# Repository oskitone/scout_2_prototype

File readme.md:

# scout_2_prototype

This is a prototype around a PCB I sent off to fab in March 2022... that I'm slowly bringing back to life. I'm kind of using it as a springboard for the next thing, whatever that is and whenever it happens!

Very much work-in-progress. License will be MIT like other kits.

Forked from scout's [2-25_keys](https://github.com/oskitone/scout/tree/2-25_keys) branch

## In this repo

- Kicad project
- OpenSCAD for scaffolding and keys models
- STLs for 3D-printing

## Goals

### Overarching Oskitone design goals

- Easy to solder. Only through-hole parts, even if it limits functionality.
- Easy to change. Code can be edited with free software and cheap hardware.
- Easy to play. No hidden menus, secret key combos, or overloading. One control per one function.
- Easy to understand. Code should be relatively accessible to anybody familiar with Arduino.
- Easy to hack. Programming header (TODO? hmm), usual open source ethos stuff.

### And specific to the next ~synth

- Polyphony
  - Per my ability, four is a reasonable number of notes to play simultaneously. Three is okay but would be frustrating. Two would be funny?
  - Anyway, four notes is what D9-12 are attempting. At the time, I was thinking I could tack some math around millis() and make the square waves manually... maybe use an interrupt timer? My pin choice seems random, and there're probably better choices.
- Any kind of musical connectivity
  - MIDI
    - USB is modern but circular DIN connectors are standard and inarguably answer the question "But can it do MIDI?!"
    - I think I'd also need non-DIP chips to do USB MIDI so that's out
    - I don't know if both IN and OUT are necessary or which to prefer if there can only be one. DIN connectors are big; [TRS MIDI](https://minimidi.world/) is an option.
  - Control Voltage
    - I'm open to this but don't really know the scene well enough to know what would be good. If it's easy to add, sure.
- Support for Mozzi w/o shipping w/ it
  - I want it to still feel solidly like an Oskitone instrument, for better and no doubt worse. Blame ["not invented here" syndrome](https://en.wikipedia.org/wiki/Not_invented_here).
  - Mozzi is cool as hell but it does require reading docs, which maybe breaks the "easy to understand" goal.
  - <del>Plus, even if I wanted to, I don't think Mozzi's license would permit me selling kits w/ it.</del> [Looks like they're GNU LGPL now](https://github.com/sensorium/Mozzi/pull/240), so may be okay.
  - That having been said, I want to engender "side-loading" things like this and make swapping to Mozzi straightforward, especially if the barrier to entry is low. So minimally it needs the right pins, an output filter, maybe other changes too.
- More musically useful than the Scout
  - Same size keys but as many as I can fit on a Prusa.
  - A semblance of control with analog input pots. Currently doing octave and glide.
  - Glide is fun but will be weird if/when polyphony is introduced. Could do poly only at 0 glide

## TODO / known issues / things for next rev

- 3D prints
  - Octave control really needs detents or some kinda tactile feedback on rotation.
- For next rev
  - More key mounting screw holes? Key bed subassembly with multiple parts
  - Rethink headphone output in signal path to minimize amplified noise
  - 386 bass boost?
  - Fix PROOF silkscreen text on back
  - Try shift register for 8 outputs? To resistor array!
  - Ditch MIDI in. Keep MIDI out but use TRS for smaller footprint
  - See if speaker can fit in new space?
- Tiny speaker is quick to distort and has no low end
- Make it clear/explicit how FUNCTION_INDICATOR_LED is used as "hanging" indicator. Right now, it's incidental.

Anything else?

https://github.com/user-attachments/assets/99f4f9d2-c58f-4821-b225-9032d2b2e849

## Uploading new code

The UART header [works the same as the OG Scout](https://oskitone.github.io/scout/change-the-arduino-code).

The cable's black wire should be on the left and green on the right.

## BOM

| Designator           | Footprint                                         | Quantity | Designation        |
| -------------------- | ------------------------------------------------- | -------- | ------------------ |
| SW1-SW25             | SW_PUSH_6mm                                       | 25       | SPST               |
| BT1                  | PinHeader_1x02_P2.54mm_Vertical                   | 1        | 4.5v               |
| LS1                  | PinHeader_1x02_P2.54mm_Vertical                   | 1        | Speaker            |
| RV1                  | Potentiometer_Bourns_PTV09A-1_Single_Vertical     | 1        | 10k Log            |
| Y1                   | Resonator-3Pin_W7.0mm_H2.5mm                      | 1        | 16.00MHz           |
| U2                   | DIP-8_W7.62mm                                     | 1        | LM386              |
| R4,R5,R7,R6          | R_Axial_DIN0207_L6.3mm_D2.5mm_P10.16mm_Horizontal | 4        | 10K                |
| J1                   | AUDIO-JACK                                        | 1        | AudioJack2_SwitchT |
| C2,C4,C5             | C_Disc_D5.0mm_W2.5mm_P5.00mm                      | 3        | .1uF               |
| C6,C1                | CP_Radial_D8.0mm_P3.50mm                          | 2        | 220uF              |
| U1                   | DIP-28_W7.62mm                                    | 1        | ATmega328P-PU      |
| D1-D25,D27           | D_DO-41_SOD81_P10.16mm_Horizontal                 | 26       | D                  |
| J2                   | PinHeader_1x06_P2.54mm_Horizontal                 | 1        | Conn_01x06_Male    |
| R8                   | R_Axial_DIN0207_L6.3mm_D2.5mm_P10.16mm_Horizontal | 1        | 1m                 |
| R9,R13               | R_Axial_DIN0207_L6.3mm_D2.5mm_P10.16mm_Horizontal | 2        | 10k                |
| R10,R1,R11,R3,R2,R12 | R_Axial_DIN0207_L6.3mm_D2.5mm_P10.16mm_Horizontal | 6        | 220                |
| D26                  | LED_D5.0mm-4_RGB_Staggered_Pins                   | 1        | LED_CRGB           |
| J4,J3                | DIN5-RA-PTH                                       | 2        | DIN5               |
| SW26                 | SW_Slide_1P2T_CK_OS102011MS2Q                     | 1        | SW_SPST            |
| RV2,RV3              | Potentiometer_Bourns_PTV09A-1_Single_Vertical     | 2        | 10k                |
| C3                   | CP_Radial_D5.0mm_P2.00mm                          | 1        | 1uF                |
| U3                   | DIP-8_W7.62mm                                     | 1        | 6N138              |

## Schematics

TODO: update to PROOF B

## 3D Models

Normally I'd put them on thingiverse/etc, but here they're included in the repo in the `stls` folder.

### OpenSCAD dependencies

Assumes `parts_cafe` is in a sibling directory and is up to date on the `main` branch. Here's how I've got it:

    \ oskitone
        \ parts_cafe
        \ scout_2_prototype

You'll also need to install the [Orbitron](https://fonts.google.com/specimen/Orbitron) font.

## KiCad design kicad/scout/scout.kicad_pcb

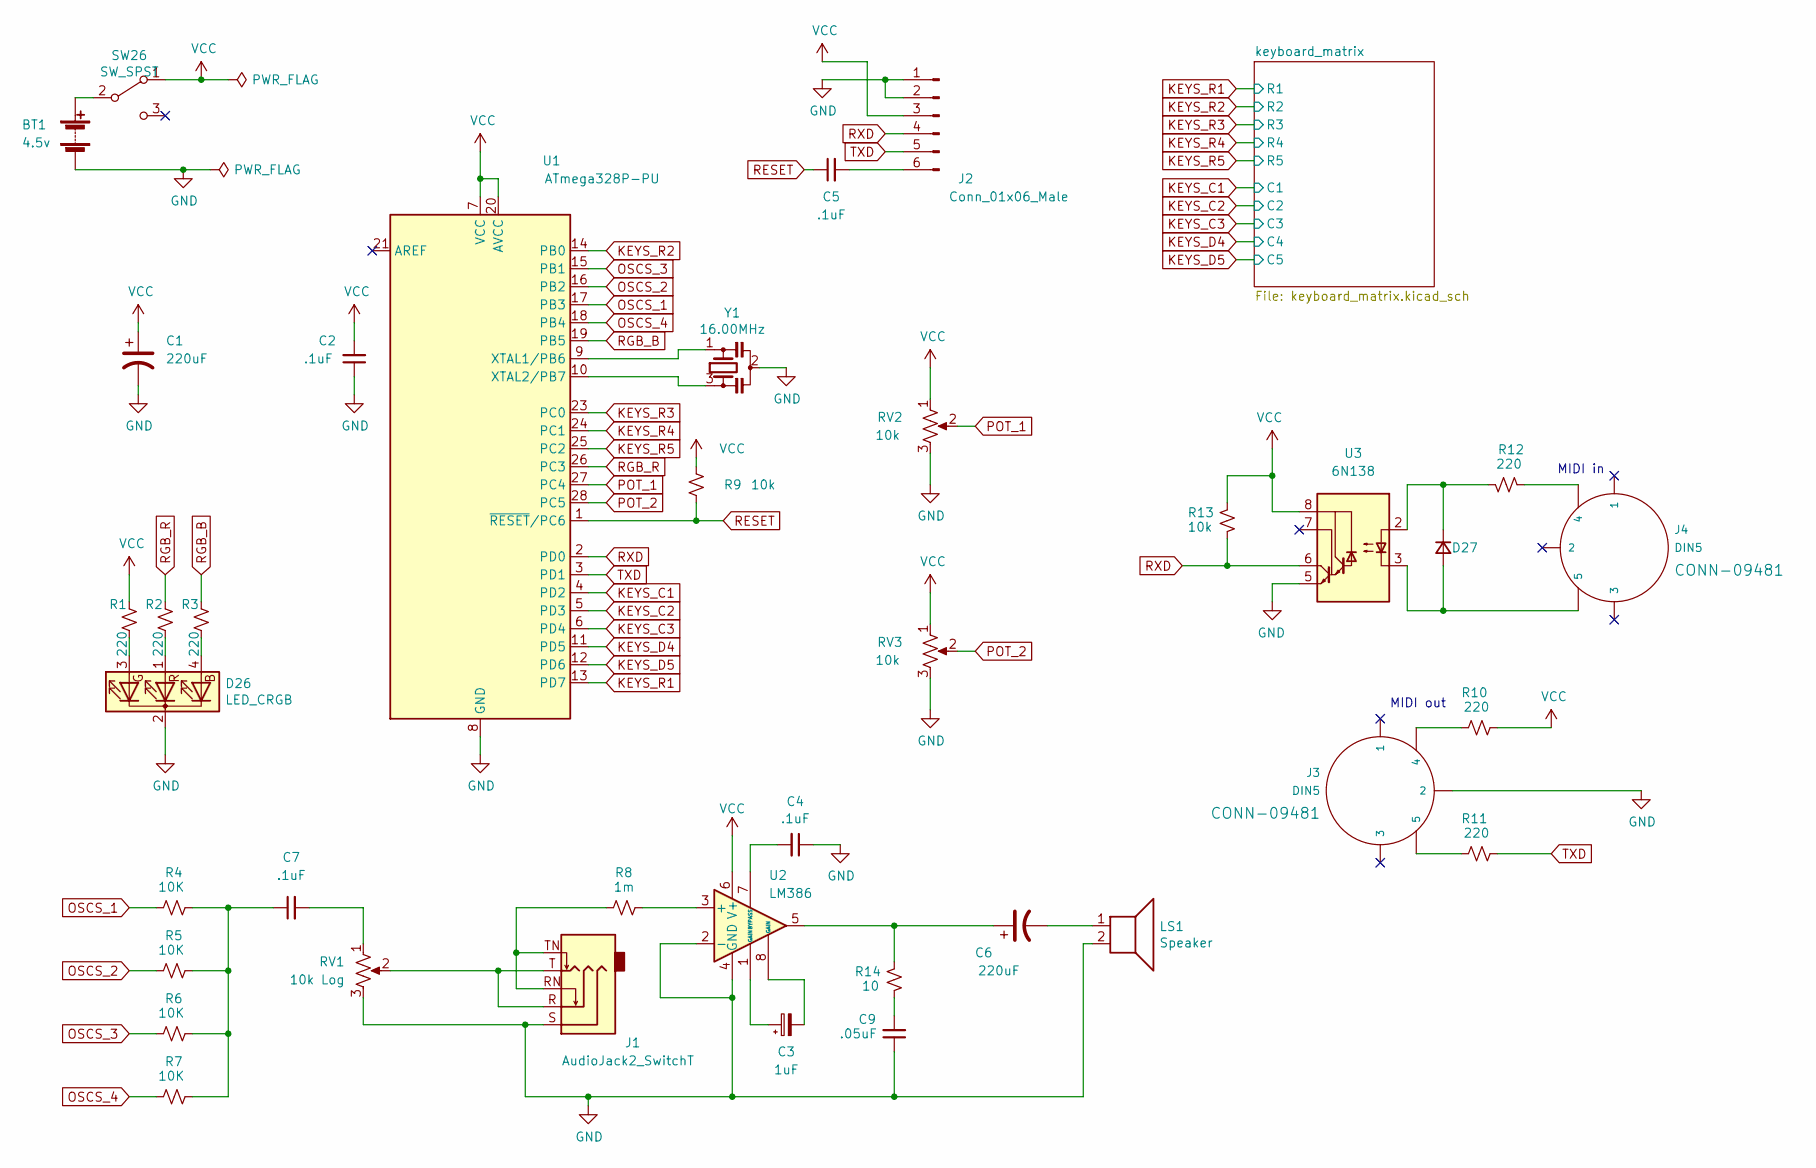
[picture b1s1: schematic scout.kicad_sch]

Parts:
BT1: 4.5v; PinHeader_1x02_P2.54mm_Vertical
C1, C6: 220uF; CP_Radial_D8.0mm_P3.50mm
C2, C4, C5, C7: .1uF; C_Disc_D5.0mm_W2.5mm_P5.00mm
C3: 1uF; CP_Radial_D5.0mm_P2.00mm
C9: .05uF; C_Disc_D5.0mm_W2.5mm_P5.00mm
D26: LED_CRGB; LED_D5.0mm-4_RGB_Staggered_Pins
D27: D; D_DO-41_SOD81_P10.16mm_Horizontal
J1: AudioJack2_SwitchT; AUDIO-JACK
J2: Conn_01x06_Male; PinHeader_1x06_P2.54mm_Horizontal
J3, J4: DIN5; DIN5-RA-PTH
LS1: Speaker; PinHeader_1x02_P2.54mm_Vertical
R1, R2, R3, R10, R11, R12: 220; R_Axial_DIN0207_L6.3mm_D2.5mm_P10.16mm_Horizontal
R4, R5, R6, R7: 10K; R_Axial_DIN0207_L6.3mm_D2.5mm_P10.16mm_Horizontal
R8: 1m; R_Axial_DIN0207_L6.3mm_D2.5mm_P10.16mm_Horizontal
R9, R13: 10k; R_Axial_DIN0207_L6.3mm_D2.5mm_P10.16mm_Horizontal
R14: 10; R_Axial_DIN0207_L6.3mm_D2.5mm_P10.16mm_Horizontal
RV1: 10k Log; Potentiometer_Bourns_PTV09A-1_Single_Vertical
RV2, RV3: 10k; Potentiometer_Bourns_PTV09A-1_Single_Vertical
SW26: SW_SPST; SW_Slide_1P2T_CK_OS102011MS2Q
U1: ATmega328P-PU; DIP-28_W7.62mm
U2: LM386; DIP-8_W7.62mm
U3: 6N138; DIP-8_W7.62mm
Y1: 16.00MHz; Resonator-3Pin_W7.0mm_H2.5mm

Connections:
GND: BT1.2 (-), C1.2, C2.1, C4.1, C9.1, D26.2 (K), J1.S, J2.1, J2.2, J3.2, LS1.2, RV1.3, RV2.3, RV3.3, U1.8 (GND), U1.22 (GND), U2.2 (-), U2.4 (GND), U3.5 (GND), Y1.2
KEYS_C1: U1.4 (PD2); also elsewhere on the board
KEYS_C2: U1.5 (PD3); also elsewhere on the board
KEYS_C3: U1.6 (PD4); also elsewhere on the board
KEYS_D4: U1.11 (PD5); also elsewhere on the board
KEYS_D5: U1.12 (PD6); also elsewhere on the board
KEYS_R1: U1.13 (PD7); also elsewhere on the board
KEYS_R2: U1.14 (PB0); also elsewhere on the board
KEYS_R3: U1.23 (PC0); also elsewhere on the board
KEYS_R4: U1.24 (PC1); also elsewhere on the board
KEYS_R5: U1.25 (PC2); also elsewhere on the board
unnamed: BT1.1 (+), SW26.2 (B)
unnamed: C3.1, U2.1 (GAIN)
unnamed: C3.2, U2.8 (GAIN)
unnamed: C6.1, R14.1, U2.5
unnamed: C6.2, LS1.1
unnamed: C7.1, R4.2, R5.2, R6.2, R7.2
unnamed: C7.2, RV1.1
unnamed: C9.2, R14.2
unnamed: D26.4 (BA), R3.2
unnamed: D26.1 (GA), R2.2
unnamed: D26.3 (RA), R1.2
unnamed: D27.2 (A), J4.5, U3.3 (C2)
unnamed: D27.1 (K), R12.2, U3.2 (C1)
unnamed: J1.R, J1.T, RV1.2
unnamed: J1.RN, J1.TN, R8.1
unnamed: C5.2, J2.6
unnamed: J3.4, R10.1
unnamed: J3.5, R11.1
unnamed: J4.4, R12.1
unnamed: U1.9 (XTAL1/PB6), Y1.1
unnamed: U1.10 (XTAL2/PB7), Y1.3
unnamed: R8.2, U2.3 (+)
unnamed: C4.2, U2.7 (BYPASS)
OSCS_1: R4.1, U1.17 (PB3)
OSCS_2: R5.1, U1.16 (PB2)
OSCS_3: R6.1, U1.15 (PB1)
OSCS_4: R7.1, U1.18 (PB4)
POT_1: RV2.2, U1.27 (PC4)
POT_2: RV3.2, U1.28 (PC5)
RESET: C5.1, R9.2, U1.1 (~RESET/PC6)
RGB_B: R3.1, U1.19 (PB5)
RGB_R: R2.1, U1.26 (PC3)
RXD: J2.4, R13.2, U1.2 (PD0), U3.6 (VO2)
TXD: J2.5, R11.2, U1.3 (PD1)
VCC: C1.1, C2.2, J2.3, R1.1, R9.1, R10.2, R13.1, RV2.1, RV3.1, SW26.1 (A), U1.7 (VCC), U1.20 (AVCC), U2.6 (V+), U3.8 (VCC)

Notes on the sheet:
MIDI in
MIDI out

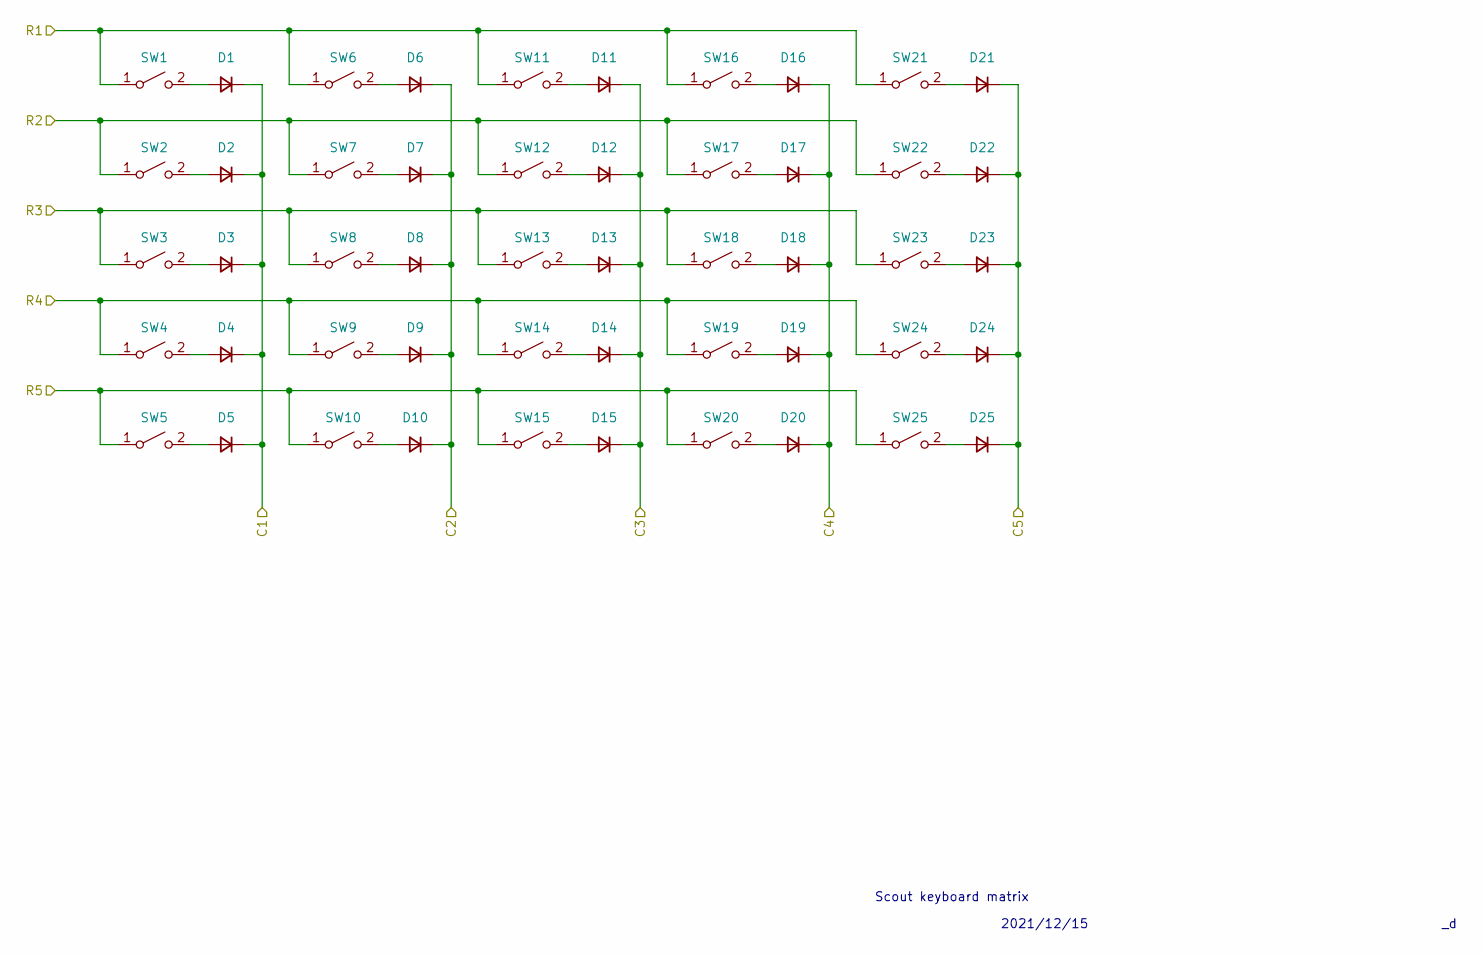
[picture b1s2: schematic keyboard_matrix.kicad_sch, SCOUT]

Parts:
D1, D2, D3, D4, D5, D6, D7, D8, D9, D10, D11, D12, D13, D14, D15, D16, D17, D18, D19, D20, D21, D22, D23, D24, D25: 1N4148; D_DO-41_SOD81_P10.16mm_Horizontal
SW1, SW2, SW3, SW4, SW5, SW6, SW7, SW8, SW9, SW10, SW11, SW12, SW13, SW14, SW15, SW16, SW17, SW18, SW19, SW20, SW21, SW22, SW23, SW24, SW25: SPST; SW_PUSH_6mm

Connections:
KEYS_C1: D1.1 (K), D2.1 (K), D3.1 (K), D4.1 (K), D5.1 (K); also elsewhere on the board
KEYS_C2: D6.1 (K), D7.1 (K), D8.1 (K), D9.1 (K), D10.1 (K); also elsewhere on the board
KEYS_C3: D11.1 (K), D12.1 (K), D13.1 (K), D14.1 (K), D15.1 (K); also elsewhere on the board
KEYS_D4: D16.1 (K), D17.1 (K), D18.1 (K), D19.1 (K), D20.1 (K); also elsewhere on the board
KEYS_D5: D21.1 (K), D22.1 (K), D23.1 (K), D24.1 (K), D25.1 (K); also elsewhere on the board
KEYS_R1: SW1.1 (A), SW6.1 (A), SW11.1 (A), SW16.1 (A), SW21.1 (A); also elsewhere on the board
KEYS_R2: SW2.1 (A), SW7.1 (A), SW12.1 (A), SW17.1 (A), SW22.1 (A); also elsewhere on the board
KEYS_R3: SW3.1 (A), SW8.1 (A), SW13.1 (A), SW18.1 (A), SW23.1 (A); also elsewhere on the board
KEYS_R4: SW4.1 (A), SW9.1 (A), SW14.1 (A), SW19.1 (A), SW24.1 (A); also elsewhere on the board
KEYS_R5: SW5.1 (A), SW10.1 (A), SW15.1 (A), SW20.1 (A), SW25.1 (A); also elsewhere on the board
unnamed: D1.2 (A), SW1.2 (B)
unnamed: D2.2 (A), SW2.2 (B)
unnamed: D3.2 (A), SW3.2 (B)
unnamed: D4.2 (A), SW4.2 (B)
unnamed: D5.2 (A), SW5.2 (B)
unnamed: D6.2 (A), SW6.2 (B)
unnamed: D7.2 (A), SW7.2 (B)
unnamed: D8.2 (A), SW8.2 (B)
unnamed: D9.2 (A), SW9.2 (B)
unnamed: D10.2 (A), SW10.2 (B)
unnamed: D11.2 (A), SW11.2 (B)
unnamed: D12.2 (A), SW12.2 (B)
unnamed: D13.2 (A), SW13.2 (B)
unnamed: D14.2 (A), SW14.2 (B)
unnamed: D15.2 (A), SW15.2 (B)
unnamed: D16.2 (A), SW16.2 (B)
unnamed: D17.2 (A), SW17.2 (B)
unnamed: D18.2 (A), SW18.2 (B)
unnamed: D19.2 (A), SW19.2 (B)
unnamed: D20.2 (A), SW20.2 (B)
unnamed: D21.2 (A), SW21.2 (B)
unnamed: D22.2 (A), SW22.2 (B)
unnamed: D23.2 (A), SW23.2 (B)
unnamed: D24.2 (A), SW24.2 (B)
unnamed: D25.2 (A), SW25.2 (B)

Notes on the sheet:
2021/12/15
Scout keyboard matrix

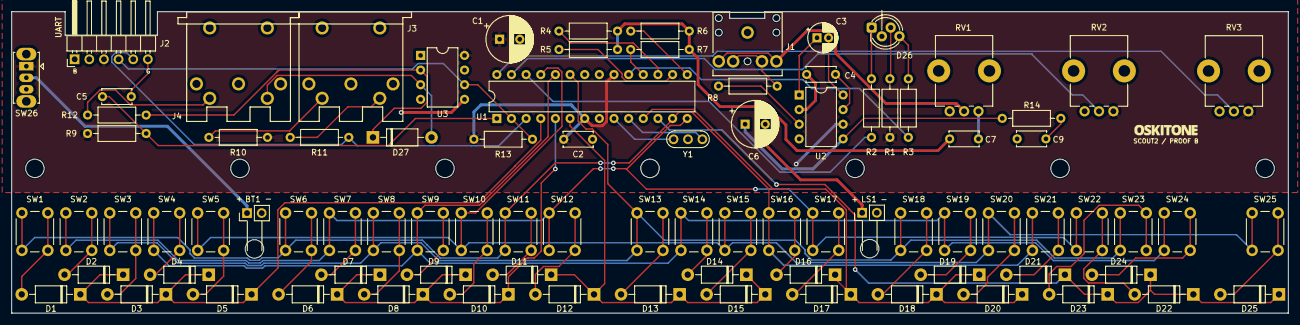
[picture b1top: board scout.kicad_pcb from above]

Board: 2 copper layers, 221.4 x 52.3 mm, 98 parts (0 on the bottom side), 71 nets.

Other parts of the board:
 : MountingHole_3.2mm_M3
 #2,  #3,  #4,  #5,  #6,  #7,  #8,  #9: MountingHole_3.2mm_M3
Ref**: Val**; branding

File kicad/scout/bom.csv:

"Id";"Designator";"Footprint";"Quantity";"Designation";"Supplier and ref";
1;"SW4,SW10,SW2,SW3,SW5,SW6,SW7,SW8,SW9,SW11,SW12,SW13,SW14,SW15,SW16,SW17,SW18,SW1,SW24,SW19,SW20,SW22,SW21,SW25,SW23";"SW_PUSH_6mm";25;"SPST";;;
2;"BT1";"PinHeader_1x02_P2.54mm_Vertical";1;"4.5v";;;
3;"LS1";"PinHeader_1x02_P2.54mm_Vertical";1;"Speaker";;;
4;"RV1";"Potentiometer_Bourns_PTV09A-1_Single_Vertical";1;"10k Log";;;
5;"Y1";"Resonator-3Pin_W7.0mm_H2.5mm";1;"16.00MHz";;;
6;"U2";"DIP-8_W7.62mm";1;"LM386";;;
7;"R4,R5,R7,R6";"R_Axial_DIN0207_L6.3mm_D2.5mm_P10.16mm_Horizontal";4;"10K";;;
8;"J1";"AUDIO-JACK";1;"AudioJack2_SwitchT";;;
9;"Ref**";"logo";1;"Val**";;;
10;"C2,C4,C5";"C_Disc_D5.0mm_W2.5mm_P5.00mm";3;".1uF";;;
11;"C6,C1";"CP_Radial_D8.0mm_P3.50mm";2;"220uF";;;
12;"U1";"DIP-28_W7.62mm";1;"ATmega328P-PU";;;
13;"D1,D14,D24,D25,D7,D17,D12,D13,D18,D15,D4,D22,D11,D6,D19,D2,D20,D27,D9,D10,D5,D16,D23,D3,D21,D8";"D_DO-41_SOD81_P10.16mm_Horizontal";26;"D";;;
14;"J2";"PinHeader_1x06_P2.54mm_Horizontal";1;"Conn_01x06_Male";;;
15;"Ref**";"branding";1;"Val**";;;
16;"R8";"R_Axial_DIN0207_L6.3mm_D2.5mm_P10.16mm_Horizontal";1;"1m";;;
17;"R9,R13";"R_Axial_DIN0207_L6.3mm_D2.5mm_P10.16mm_Horizontal";2;"10k";;;
18;"R10,R1,R11,R3,R2,R12";"R_Axial_DIN0207_L6.3mm_D2.5mm_P10.16mm_Horizontal";6;"220";;;
19;"D26";"LED_D5.0mm-4_RGB_Staggered_Pins";1;"LED_CRGB";;;
20;"J4,J3";"DIN5-RA-PTH";2;"DIN5";;;
21;"SW26";"SW_Slide_1P2T_CK_OS102011MS2Q";1;"SW_SPST";;;
22;"RV2,RV3";"Potentiometer_Bourns_PTV09A-1_Single_Vertical";2;"10k";;;
23;"C3";"CP_Radial_D5.0mm_P2.00mm";1;"1uF";;;
24;"U3";"DIP-8_W7.62mm";1;"6N138";;;

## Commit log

2025-03-09 Copy over relevant scout repo stuff
    Commit d72051ae, the scout_2_protoype PCB but
    no code changes
2025-03-09 Hack Arduino code to feature ~parity
2025-03-09 Copy over parts_cafe stuff
    From branch scout_2_pcb_base commit 9b94313,
    prototype_pcb_assembly renamed scout_2_prototype
2025-03-09 START Edit readme
2025-03-10 Elevate PCB from battery_holder more
    Turns out derived clearance wasn't enough and
    pins were shorting against batteries...
2025-03-10 Support PCB in the back
2025-03-10 Fillet keys on render
2025-03-12 Update to latest kicad
    No changes otherwise
2025-03-12 Update schematic
    Should be no changes to function or PCB...
    * Note pin assignments
    * Tidy RV2 and RV3 voltage dividers
    * Have MIDI read left to right
    * Specify 1N4148 diodes
    And add to readme
2025-03-12 Update readme
    * Do some TODOs
    * Add some pics
    * Misc text cleanup
2025-03-12 Add final-assembly-timelapse to readme
2025-03-12 Doc BOM
2025-03-14 Doc OpenSCAD dependencies
2025-03-14 Stub simple deploy script
    to avoid Arduino IDE
2025-03-14 Tidy
    * Drop some odd comments
    * Do a TODO about LEDs
    * Adopt clang formatting
2025-03-15 Note UART header orientation
2025-03-21 Replace tone() with a Timer2 ISR that toggles the for speaker I/O
    Very hacky, gets out of tune.
2025-03-21 4-note polyphony. Broken glides. Out of tune. But it's a start.
2025-03-21 Glides work.
    There's a weird bug but I think it's about how the key buffer gets populated.
2025-03-21 Reverse order of keys in buffer
    Fixes glide sorting
2025-03-22 Clean up some unused/repetitive code
2025-03-22 Move tone() replacement code into separate files
2025-03-22 Add note about unrolled loop
2025-03-22 Limit octave range
    Due to timer ISR precision, the lowest pitch we can play is 122 Hz. Tuning also gets worse the higher pitch we go. Cutting off an octave at either end works around this. I would like to improve this 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
2025-03-22 Ticks now use 16 bits, adding lower octaves back
    Timing works out!
2025-03-22 Dither pitches when the ISR quantizes them
    This is a nice way to say "add vibrato for high notes." Basically, we get around the 16 us quantization by remembering how far off we are and adding that to the next trigger time.
2025-03-22 Add some comments about timing
2025-03-22 Tidying up more things into arrays
2025-03-22 Revert "Reverse order of keys in buffer"
    This reverts commit c45f9245a73179720c688cd9e9a4371b077e695c.
2025-03-22 Hide details of loading tones into the ISR behind a function
2025-03-22 Bounds checking.
2025-03-24 Suggest; ease concerns
    * Ditch vestigial ticks
    * Rename period to be accurate, if awkward
    * Tidy variables inside main loop
    * Minor formatting and renaming suggestions
2025-03-27 Attempt to self-document
    Attempt!
2025-03-27 Fix a couple readme typos
2025-03-27 Decouple buffer/oscillators max length
2025-03-27 Clang autoformat
2025-05-24 Note
2025-05-24 Fix silkscreen SVG path
2025-05-24 Rotate battery holder for easier access
2025-05-26 adding MIDI controller example
    Scout 2 MIDI Keyboard Controller
    * NoteOn and NoteOff messages for each key press
    * OCTAVE_PIN adjusts MIDI note number range
    * GLIDE_PIN controls pitch bend
    i tried to match the API from the Notes helper in the scout example to the MIDI_Notes helper.
2025-07-17 Rename arduino project to match repo
2025-07-17 Fix/paramaterize deploy script input slug
2026-04-01 Try to reduce noise and other refinements
    * Add decoupling cap before amp
    * Add snubber circuit after amp
    * Consider bass boost for next rev
    * Self-document pin connection assignments in schematic
    * Move branding text beyond key area
    * Reverse power switch direction
2026-04-27 Reduce noise
    * Throttle updateFromAnalogInputs()
    * Fix overzealous glide updates from unnecessary
    float casting
2026-04-27 Reserve polyphony for no glide
2026-04-27 Add barebones midi_test.ino

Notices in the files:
kicad/scout/scout.kicad_pcb:
Designed by Oskitone. CC BY-SA 4.0.
